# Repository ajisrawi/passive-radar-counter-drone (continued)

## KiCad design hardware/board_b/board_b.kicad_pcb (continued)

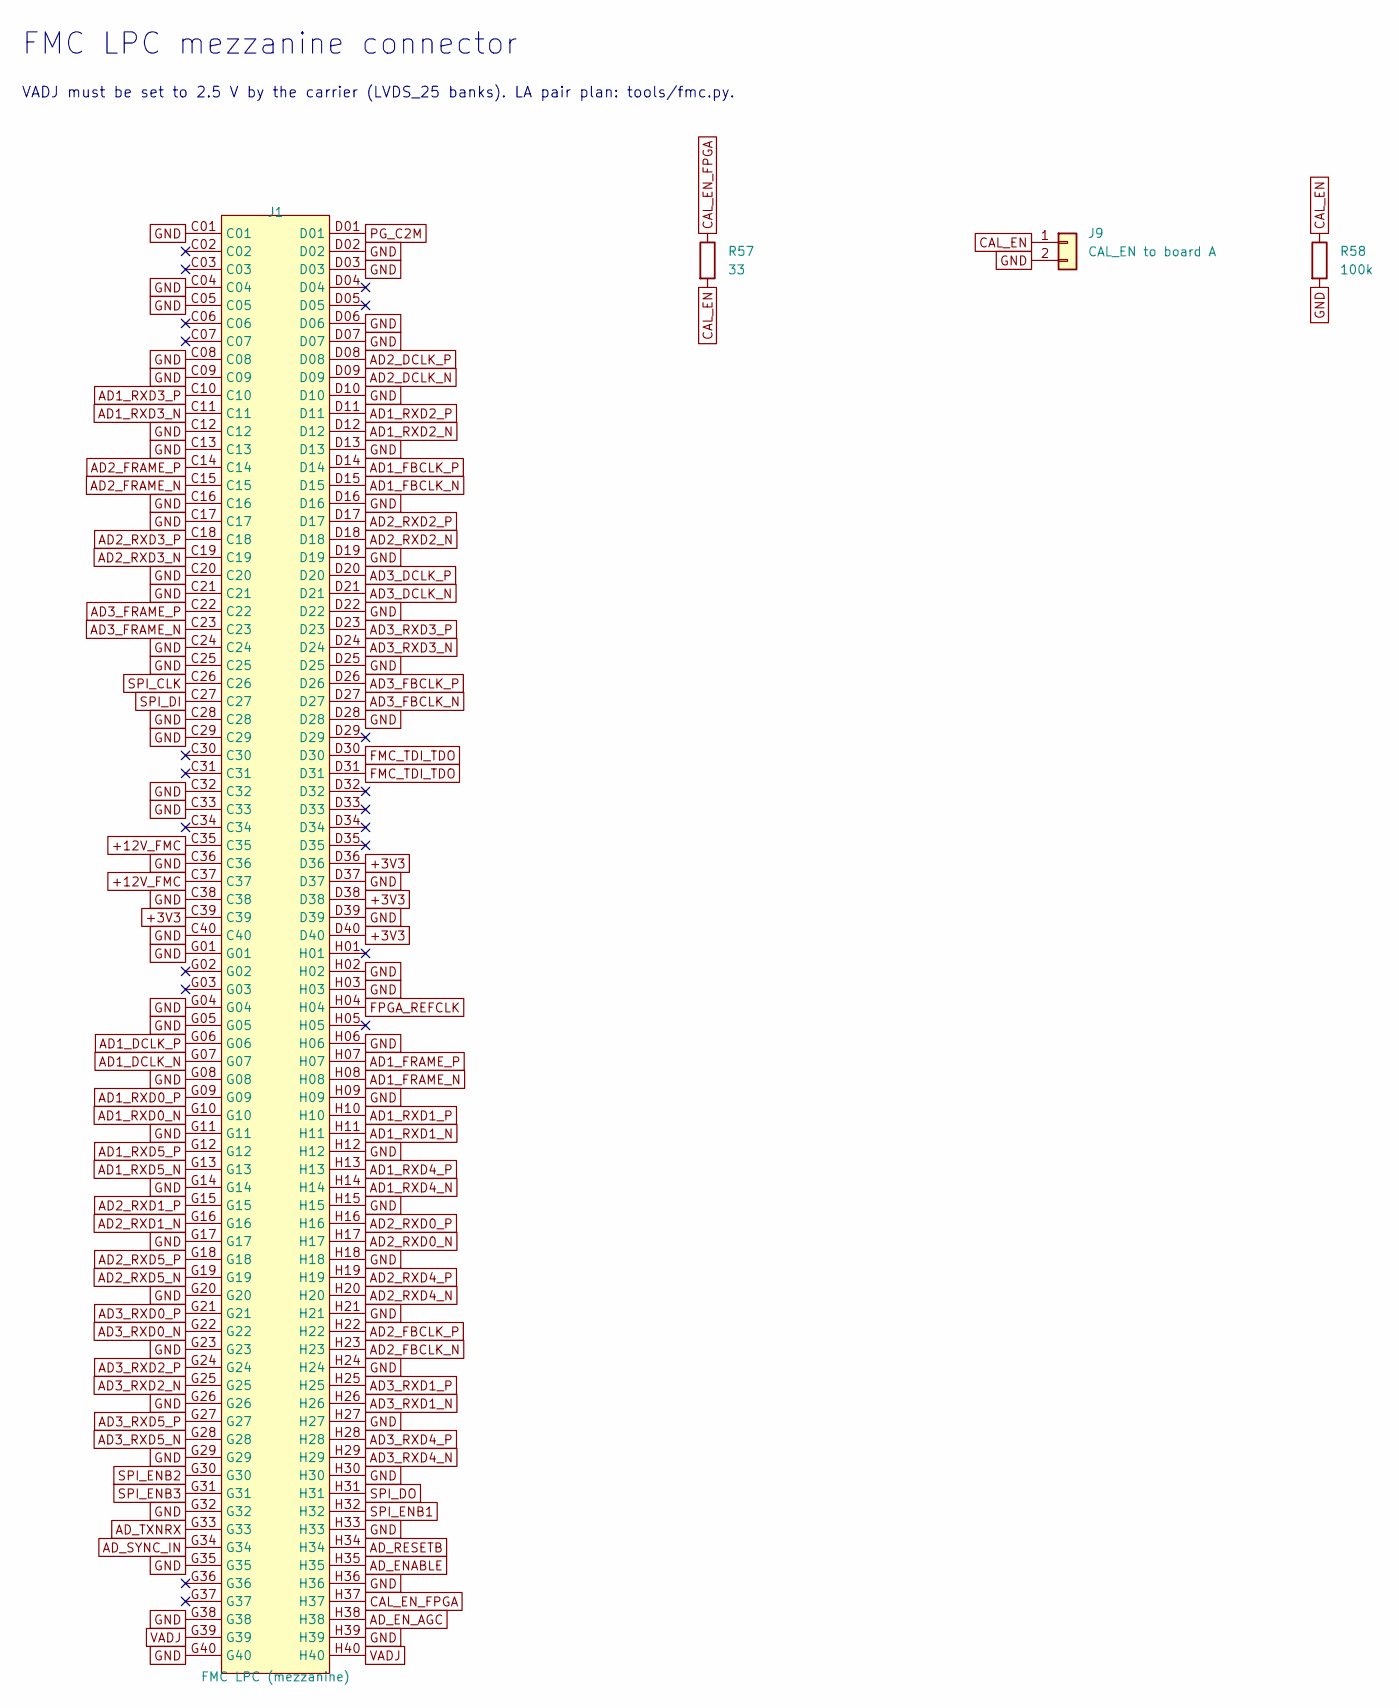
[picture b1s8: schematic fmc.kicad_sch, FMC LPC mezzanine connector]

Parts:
J1: FMC LPC (mezzanine); FPC_SMD_ASP-134604-01; MPN ASP-134604-01; LCSC C2830435
J9: CAL_EN to board A; PinHeader_1x02_P2.54mm_Vertical
R57: 33; R_0402_1005Metric
R58: 100k; R_0402_1005Metric; LCSC C25741

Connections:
+3V3: J1.C39, J1.D36, J1.D38, J1.D40; also elsewhere on the board
+12V_FMC: J1.C35, J1.C37; also elsewhere on the board
AD1_DCLK_N: J1.G07; also elsewhere on the board
AD1_DCLK_P: J1.G06; also elsewhere on the board
AD1_FBCLK_N: J1.D15; also elsewhere on the board
AD1_FBCLK_P: J1.D14; also elsewhere on the board
AD1_FRAME_N: J1.H08; also elsewhere on the board
AD1_FRAME_P: J1.H07; also elsewhere on the board
AD1_RXD0_N: J1.G10; also elsewhere on the board
AD1_RXD0_P: J1.G09; also elsewhere on the board
AD1_RXD1_N: J1.H11; also elsewhere on the board
AD1_RXD1_P: J1.H10; also elsewhere on the board
AD1_RXD2_N: J1.D12; also elsewhere on the board
AD1_RXD2_P: J1.D11; also elsewhere on the board
AD1_RXD3_N: J1.C11; also elsewhere on the board
AD1_RXD3_P: J1.C10; also elsewhere on the board
AD1_RXD4_N: J1.H14; also elsewhere on the board
AD1_RXD4_P: J1.H13; also elsewhere on the board
AD1_RXD5_N: J1.G13; also elsewhere on the board
AD1_RXD5_P: J1.G12; also elsewhere on the board
AD2_DCLK_N: J1.D09; also elsewhere on the board
AD2_DCLK_P: J1.D08; also elsewhere on the board
AD2_FBCLK_N: J1.H23; also elsewhere on the board
AD2_FBCLK_P: J1.H22; also elsewhere on the board
AD2_FRAME_N: J1.C15; also elsewhere on the board
AD2_FRAME_P: J1.C14; also elsewhere on the board
AD2_RXD0_N: J1.H17; also elsewhere on the board
AD2_RXD0_P: J1.H16; also elsewhere on the board
AD2_RXD1_N: J1.G16; also elsewhere on the board
AD2_RXD1_P: J1.G15; also elsewhere on the board
AD2_RXD2_N: J1.D18; also elsewhere on the board
AD2_RXD2_P: J1.D17; also elsewhere on the board
AD2_RXD3_N: J1.C19; also elsewhere on the board
AD2_RXD3_P: J1.C18; also elsewhere on the board
AD2_RXD4_N: J1.H20; also elsewhere on the board
AD2_RXD4_P: J1.H19; also elsewhere on the board
AD2_RXD5_N: J1.G19; also elsewhere on the board
AD2_RXD5_P: J1.G18; also elsewhere on the board
AD3_DCLK_N: J1.D21; also elsewhere on the board
AD3_DCLK_P: J1.D20; also elsewhere on the board
AD3_FBCLK_N: J1.D27; also elsewhere on the board
AD3_FBCLK_P: J1.D26; also elsewhere on the board
AD3_FRAME_N: J1.C23; also elsewhere on the board
AD3_FRAME_P: J1.C22; also elsewhere on the board
AD3_RXD0_N: J1.G22; also elsewhere on the board
AD3_RXD0_P: J1.G21; also elsewhere on the board
AD3_RXD1_N: J1.H26; also elsewhere on the board
AD3_RXD1_P: J1.H25; also elsewhere on the board
AD3_RXD2_N: J1.G25; also elsewhere on the board
AD3_RXD2_P: J1.G24; also elsewhere on the board
AD3_RXD3_N: J1.D24; also elsewhere on the board
AD3_RXD3_P: J1.D23; also elsewhere on the board
AD3_RXD4_N: J1.H29; also elsewhere on the board
AD3_RXD4_P: J1.H28; also elsewhere on the board
AD3_RXD5_N: J1.G28; also elsewhere on the board
AD3_RXD5_P: J1.G27; also elsewhere on the board
AD_ENABLE: J1.H35; also elsewhere on the board
AD_EN_AGC: J1.H38; also elsewhere on the board
AD_RESETB: J1.H34; also elsewhere on the board
AD_SYNC_IN: J1.G34; also elsewhere on the board
AD_TXNRX: J1.G33; also elsewhere on the board
CAL_EN: J9.1, R57.2, R58.1
CAL_EN_FPGA: J1.H37, R57.1
FMC_TDI_TDO: J1.D30, J1.D31
FPGA_REFCLK: J1.H04; also elsewhere on the board
GND: J1.C01, J1.C04, J1.C05, J1.C08, J1.C09, J1.C12, J1.C13, J1.C16, J1.C17, J1.C20, J1.C21, J1.C24, J1.C25, J1.C28, J1.C29, J1.C32, J1.C33, J1.C36, J1.C38, J1.C40, J1.D02, J1.D03, J1.D06, J1.D07, J1.D10, J1.D13, J1.D16, J1.D19, J1.D22, J1.D25, J1.D28, J1.D37, J1.D39, J1.G01, J1.G04, J1.G05, J1.G08, J1.G11, J1.G14, J1.G17, J1.G20, J1.G23, J1.G26, J1.G29, J1.G32, J1.G35, J1.G38, J1.G40, J1.H02, J1.H03, J1.H06, J1.H09, J1.H12, J1.H15, J1.H18, J1.H21, J1.H24, J1.H27, J1.H30, J1.H33, J1.H36, J1.H39, J9.2, R58.2; also elsewhere on the board
PG_C2M: J1.D01; also elsewhere on the board
SPI_CLK: J1.C26; also elsewhere on the board
SPI_DI: J1.C27; also elsewhere on the board
SPI_DO: J1.H31; also elsewhere on the board
SPI_ENB1: J1.H32; also elsewhere on the board
SPI_ENB2: J1.G30; also elsewhere on the board
SPI_ENB3: J1.G31; also elsewhere on the board
VADJ: J1.G39, J1.H40; also elsewhere on the board

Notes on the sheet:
FMC LPC mezzanine connector
VADJ must be set to 2.5 V by the carrier (LVDS_25 banks). LA pair plan: tools/fmc.py.

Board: 8 copper layers, 228 parts (67 on the bottom side), 166 nets, no tracks yet.

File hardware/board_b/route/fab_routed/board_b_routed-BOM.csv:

Comment,Designator,Footprint,JLCPCB Part #
1u,"C1,C7,C12,C14,C17,C19,C23,C29,C34,C36,C39,C41,C45,C51,C56,C58,C61,C63,C106,C112,C118",1,
100n,"C2,C3,C4,C5,C6,C8,C9,C10,C11,C13,C15,C16,C18,C20,C24,C25,C26,C27,C28,C30,C31,C32,C33,C35,C37,C38,C40,C42,C46,C47,C48,C49,C50,C52,C53,C54,C55,C57,C59,C60,C62,C64,C107,C113,C119",1,
100n,"C21,C22,C43,C44,C65,C66,C85,C89,C90,C92,C93,C94,C98,C101,C104,C110,C116",C_0402_1005Metric,
100p,"C67,C68,C70,C71,C73,C74,C76,C77,C79,C80,C82,C83",C_0402_1005Metric,
10u,"C86,C103,C105,C109,C111,C115,C117,C121,C123",C_0603_1608Metric,
1u,"C87,C88,C91,C122,C124",C_0402_1005Metric,
3.3n,C95,C_0402_1005Metric,
10u,"C96,C97,C120",C_0805_2012Metric,
22u,"C99,C100",C_0805_2012Metric,
10n,"C102,C108,C114",C_0402_1005Metric,
600R@100MHz,"FB1,FB2,FB3,FB4,FB5,FB6,FB7,FB8,FB9,FB10,FB11,FB12",L_0603_1608Metric,
FMC LPC (mezzanine),J1,FPC_SMD_ASP-134604-01,
RF_IN0,J2,SMA-TH_BWSMA-KE-Z001,
RF_IN1,J3,SMA-TH_BWSMA-KE-Z001,
RF_IN2,J4,SMA-TH_BWSMA-KE-Z001,
RF_IN3,J5,SMA-TH_BWSMA-KE-Z001,
RF_IN4,J6,SMA-TH_BWSMA-KE-Z001,
RF_IN5,J7,SMA-TH_BWSMA-KE-Z001,
EXT_REF,J8,SMA-TH_BWSMA-KE-Z001,
CAL_EN to board A,J9,PinHeader_1x02_P2.54mm_Vertical,
2.2u,L1,L_Bourns-SRN4018,
14.3k,"R1,R8,R11",R_0402_1005Metric,
22,"R2,R9,R12",R_0402_1005Metric,
10k,"R3,R4,R5,R6,R7,R10,R13,R32,R33,R51,R53,R55",R_0402_1005Metric,
0,"R15,R18,R21,R24,R27,R30",R_0402_1005Metric,
470,R34,R_0402_1005Metric,
1.5k,R36,R_0402_1005Metric,
33,"R37,R40,R43,R46,R57",R_0402_1005Metric,
120,"R38,R41,R44",R_0402_1005Metric,
100,"R39,R42,R45",R_0402_1005Metric,
125k,R47,R_0402_1005Metric,
100k,"R48,R49,R56,R58",R_0402_1005Metric,
16k,"R50,R52,R54",R_0402_1005Metric,
ATB2012-50011,"T1,T2,T3,T4,T5,T6",XFMR-SMD_ATB2012-50011-T000,
AD9361BBCZ,"U1,U2,U3",CSPBGA-144_L10.0-W10.0-R12-C12-P0.80-BL,
TLV75525PDBVR,U4,SOT-23-5,
LMK1C1104PWR,U5,TSSOP-8_L4.4-W3.0-P0.65-LS6.4-TL,
TPS62130RGTR,U6,VQFN-16-1EP_3x3mm_P0.5mm_EP1.68x1.68mm,
ADP1755ACPZ-R7,"U7,U8,U9",LFCSP-16_L4.0-W4.0-P0.65-BL-EP2.2,
40MHz TCXO 0.5ppm,Y1,OSC-SMD_10P-L7.0-W5.0-BL,

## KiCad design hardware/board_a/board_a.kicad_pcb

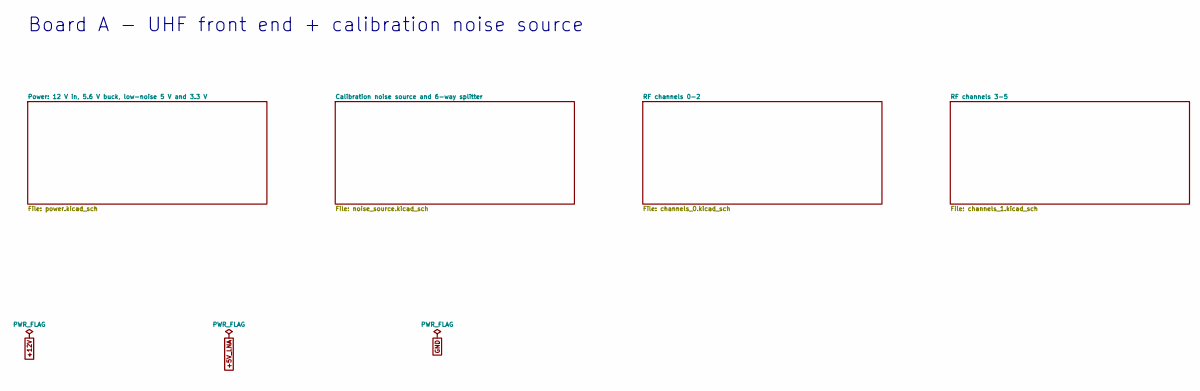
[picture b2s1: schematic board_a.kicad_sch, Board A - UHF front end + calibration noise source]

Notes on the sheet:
Board A - UHF front end + calibration noise source

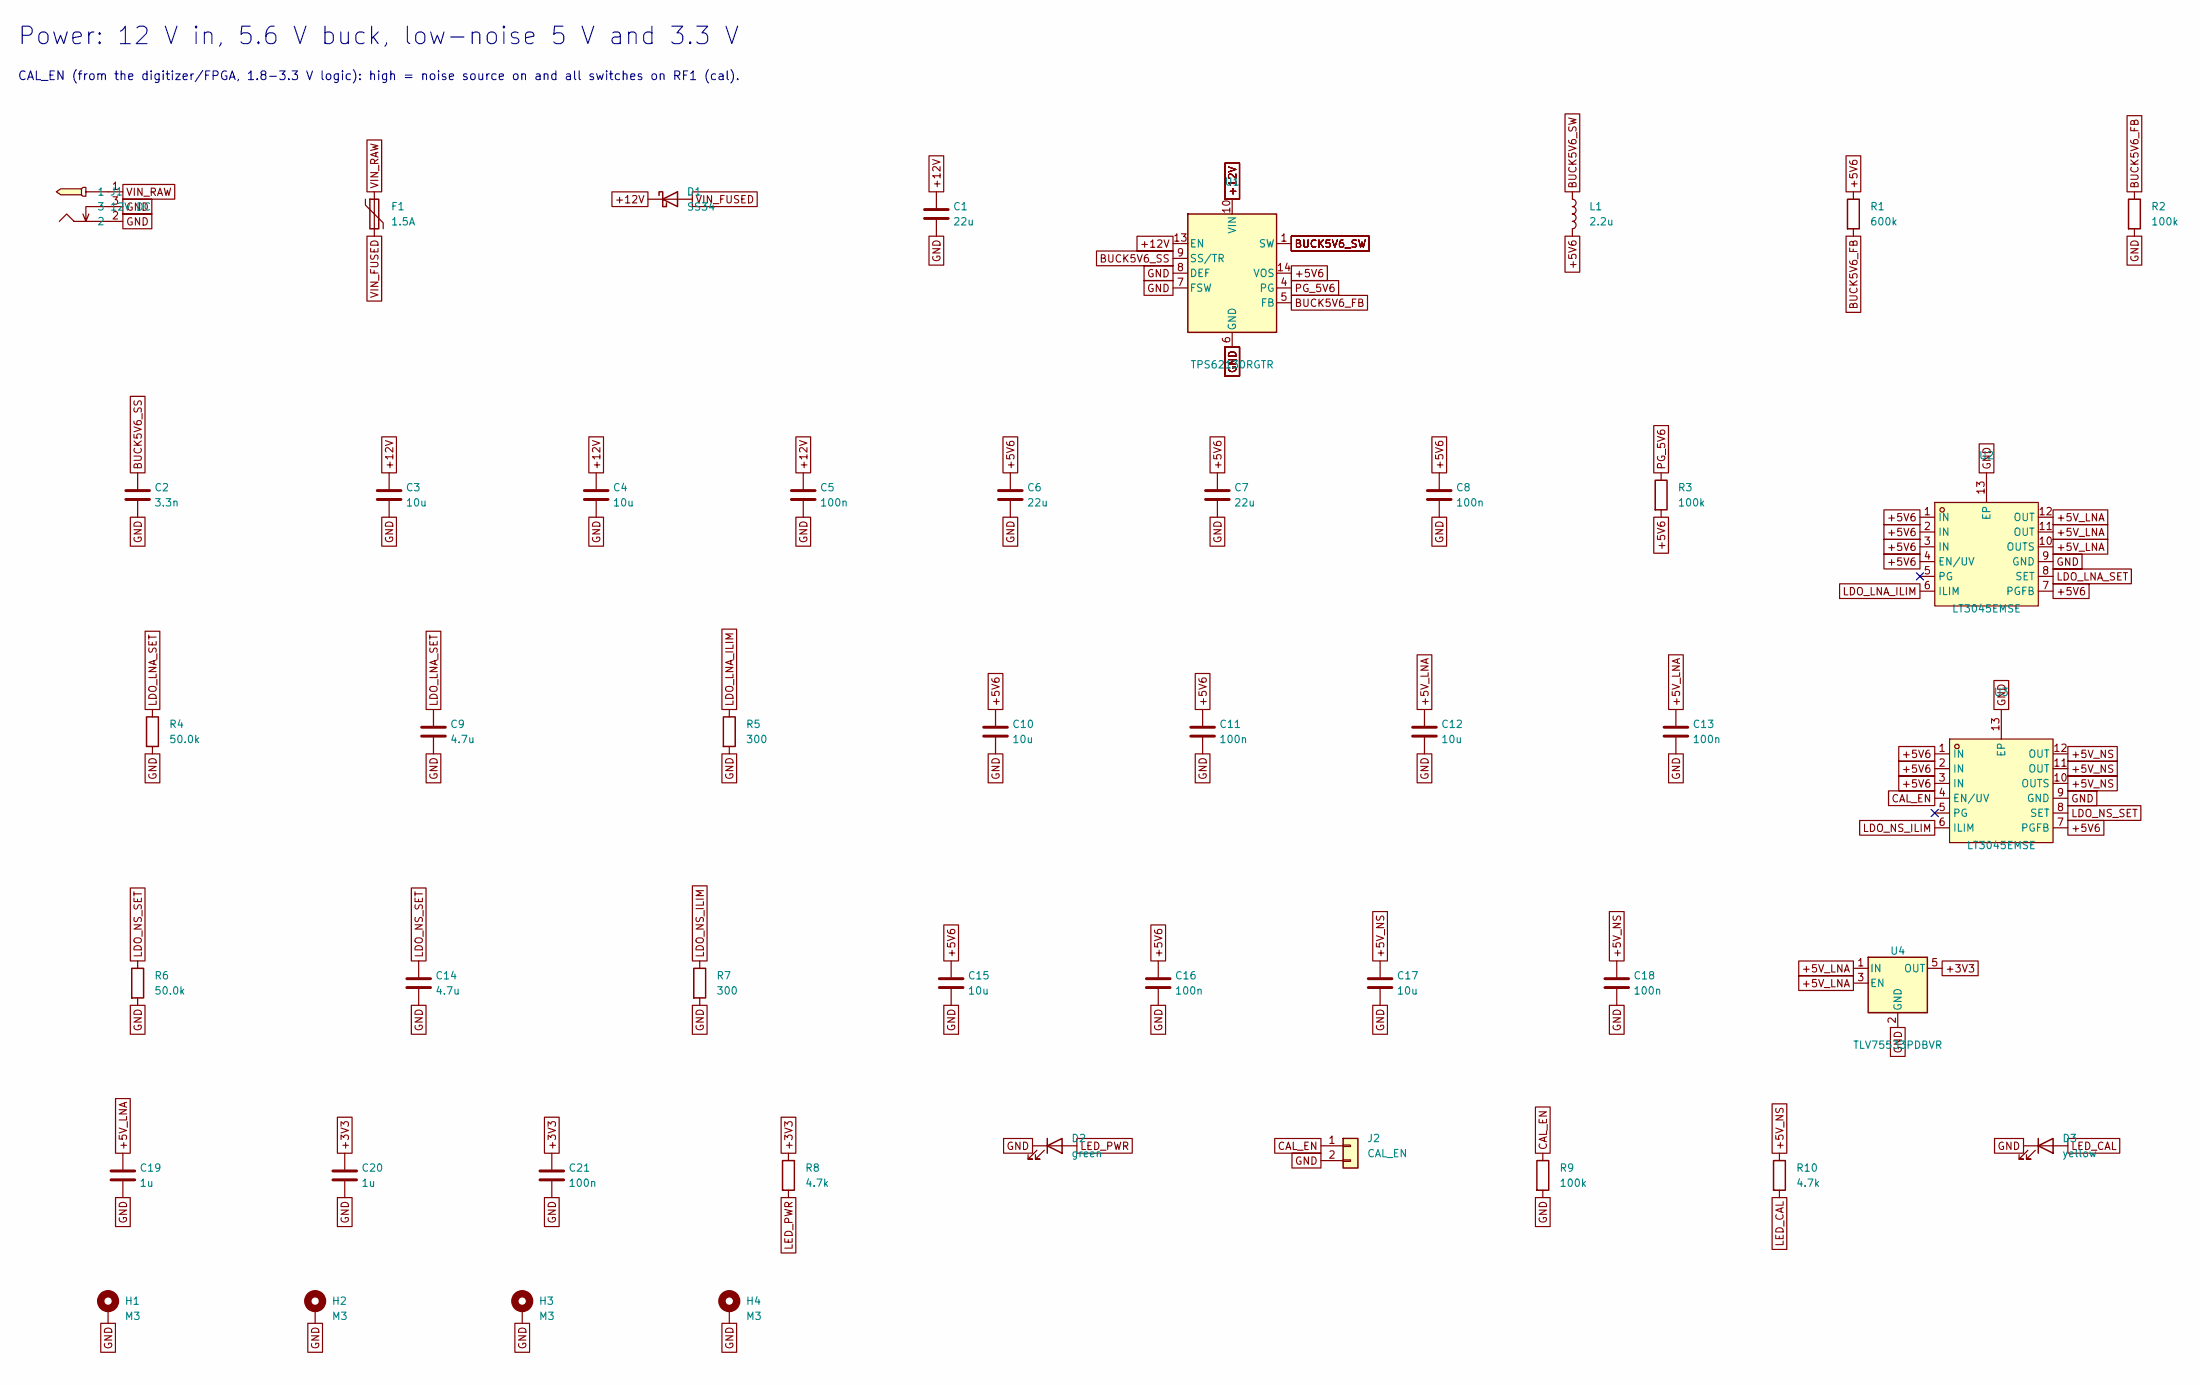
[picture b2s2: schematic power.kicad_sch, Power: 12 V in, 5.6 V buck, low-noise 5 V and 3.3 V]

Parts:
C1: 22u; C_1206_3216Metric
C2: 3.3n; C_0402_1005Metric
C3, C4: 10u; C_0805_2012Metric
C5, C8, C11, C13, C16, C18, C21: 100n; C_0402_1005Metric; LCSC C1525
C6, C7: 22u; C_0805_2012Metric; LCSC C45783
C9, C14: 4.7u; C_0603_1608Metric
C10, C12, C15, C17: 10u; C_0603_1608Metric; LCSC C19702
C19, C20: 1u; C_0402_1005Metric; LCSC C52923
D1: SS34; D_SMA; MPN SS34; LCSC C8678
D2: green; LED_0603_1608Metric
D3: yellow; LED_0603_1608Metric
F1: 1.5A; Fuse_1206_3216Metric
H1, H2, H3, H4: M3; MountingHole_3.2mm_M3_Pad_Via
J1: 12V DC; DC-IN-TH_DC-005C-20A; MPN DC-005C-20A; LCSC C84007
J2: CAL_EN; PinHeader_1x02_P2.54mm_Vertical
L1: 2.2u; L_Bourns-SRN4018; MPN SRN4018-2R2M
R1: 600k; R_0402_1005Metric
R2, R3, R9: 100k; R_0402_1005Metric; LCSC C25741
R4, R6: 50.0k; R_0402_1005Metric; Tolerance 0.1%
R5, R7: 300; R_0402_1005Metric
R8, R10: 4.7k; R_0402_1005Metric; LCSC C25900
U1: TPS62130RGTR; VQFN-16-1EP_3x3mm_P0.5mm_EP1.68x1.68mm; MPN TPS62130RGTR; LCSC C43590
U2, U3: LT3045EMSE; MSOP-12_L4.0-W3.0-P0.65-LS4.9-BL-EP; MPN LT3045EMSE#PBF; LCSC C580012
U4: TLV75533PDBVR; SOT-23-5; LCSC C404027

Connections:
+3V3: C20.1, C21.1, R8.1, U4.5 (OUT); also elsewhere on the board
+5V6: C6.1, C7.1, C8.1, C10.1, C11.1, C15.1, C16.1, L1.2, R1.1, R3.2, U1.14 (VOS), U2.1 (IN), U2.2 (IN), U2.3 (IN), U2.4 (EN/UV), U2.7 (PGFB), U3.1 (IN), U3.2 (IN), U3.3 (IN), U3.7 (PGFB)
+5V_LNA: C12.1, C13.1, C19.1, U2.10 (OUTS), U2.11 (OUT), U2.12 (OUT), U4.1 (IN), U4.3 (EN); also elsewhere on the board
+5V_NS: C17.1, C18.1, R10.1, U3.10 (OUTS), U3.11 (OUT), U3.12 (OUT); also elsewhere on the board
+12V: C1.1, C3.1, C4.1, C5.1, D1.1 (K), U1.10 (VIN), U1.11 (VIN), U1.12 (VIN), U1.13 (EN)
BUCK5V6_FB: R1.2, R2.1, U1.5 (FB)
BUCK5V6_SS: C2.1, U1.9 (SS/TR)
BUCK5V6_SW: L1.1, U1.1 (SW), U1.2 (SW), U1.3 (SW)
CAL_EN: J2.1, R9.1, U3.4 (EN/UV); also elsewhere on the board
GND: C1.2, C2.2, C3.2, C4.2, C5.2, C6.2, C7.2, C8.2, C9.2, C10.2, C11.2, C12.2, C13.2, C14.2, C15.2, C16.2, C17.2, C18.2, C19.2, C20.2, C21.2, D2.1 (K), D3.1 (K), H1.1, H2.1, H3.1, H4.1, J1.2, J1.3, J2.2, R2.2, R4.2, R5.2, R6.2, R7.2, R9.2, U1.6 (GND), U1.7 (FSW), U1.8 (DEF), U1.15 (GND), U1.16 (GND), U1.17 (GND), U2.9 (GND), U2.13 (EP), U3.9 (GND), U3.13 (EP), U4.2 (GND); also elsewhere on the board
LDO_LNA_ILIM: R5.1, U2.6 (ILIM)
LDO_LNA_SET: C9.1, R4.1, U2.8 (SET)
LDO_NS_ILIM: R7.1, U3.6 (ILIM)
LDO_NS_SET: C14.1, R6.1, U3.8 (SET)
LED_CAL: D3.2 (A), R10.2
LED_PWR: D2.2 (A), R8.2
PG_5V6: R3.1, U1.4 (PG)
VIN_FUSED: D1.2 (A), F1.2
VIN_RAW: F1.1, J1.1

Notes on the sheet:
Power: 12 V in, 5.6 V buck, low-noise 5 V and 3.3 V
CAL_EN (from the digitizer/FPGA, 1.8-3.3 V logic): high = noise source on and all switches on RF1 (cal).

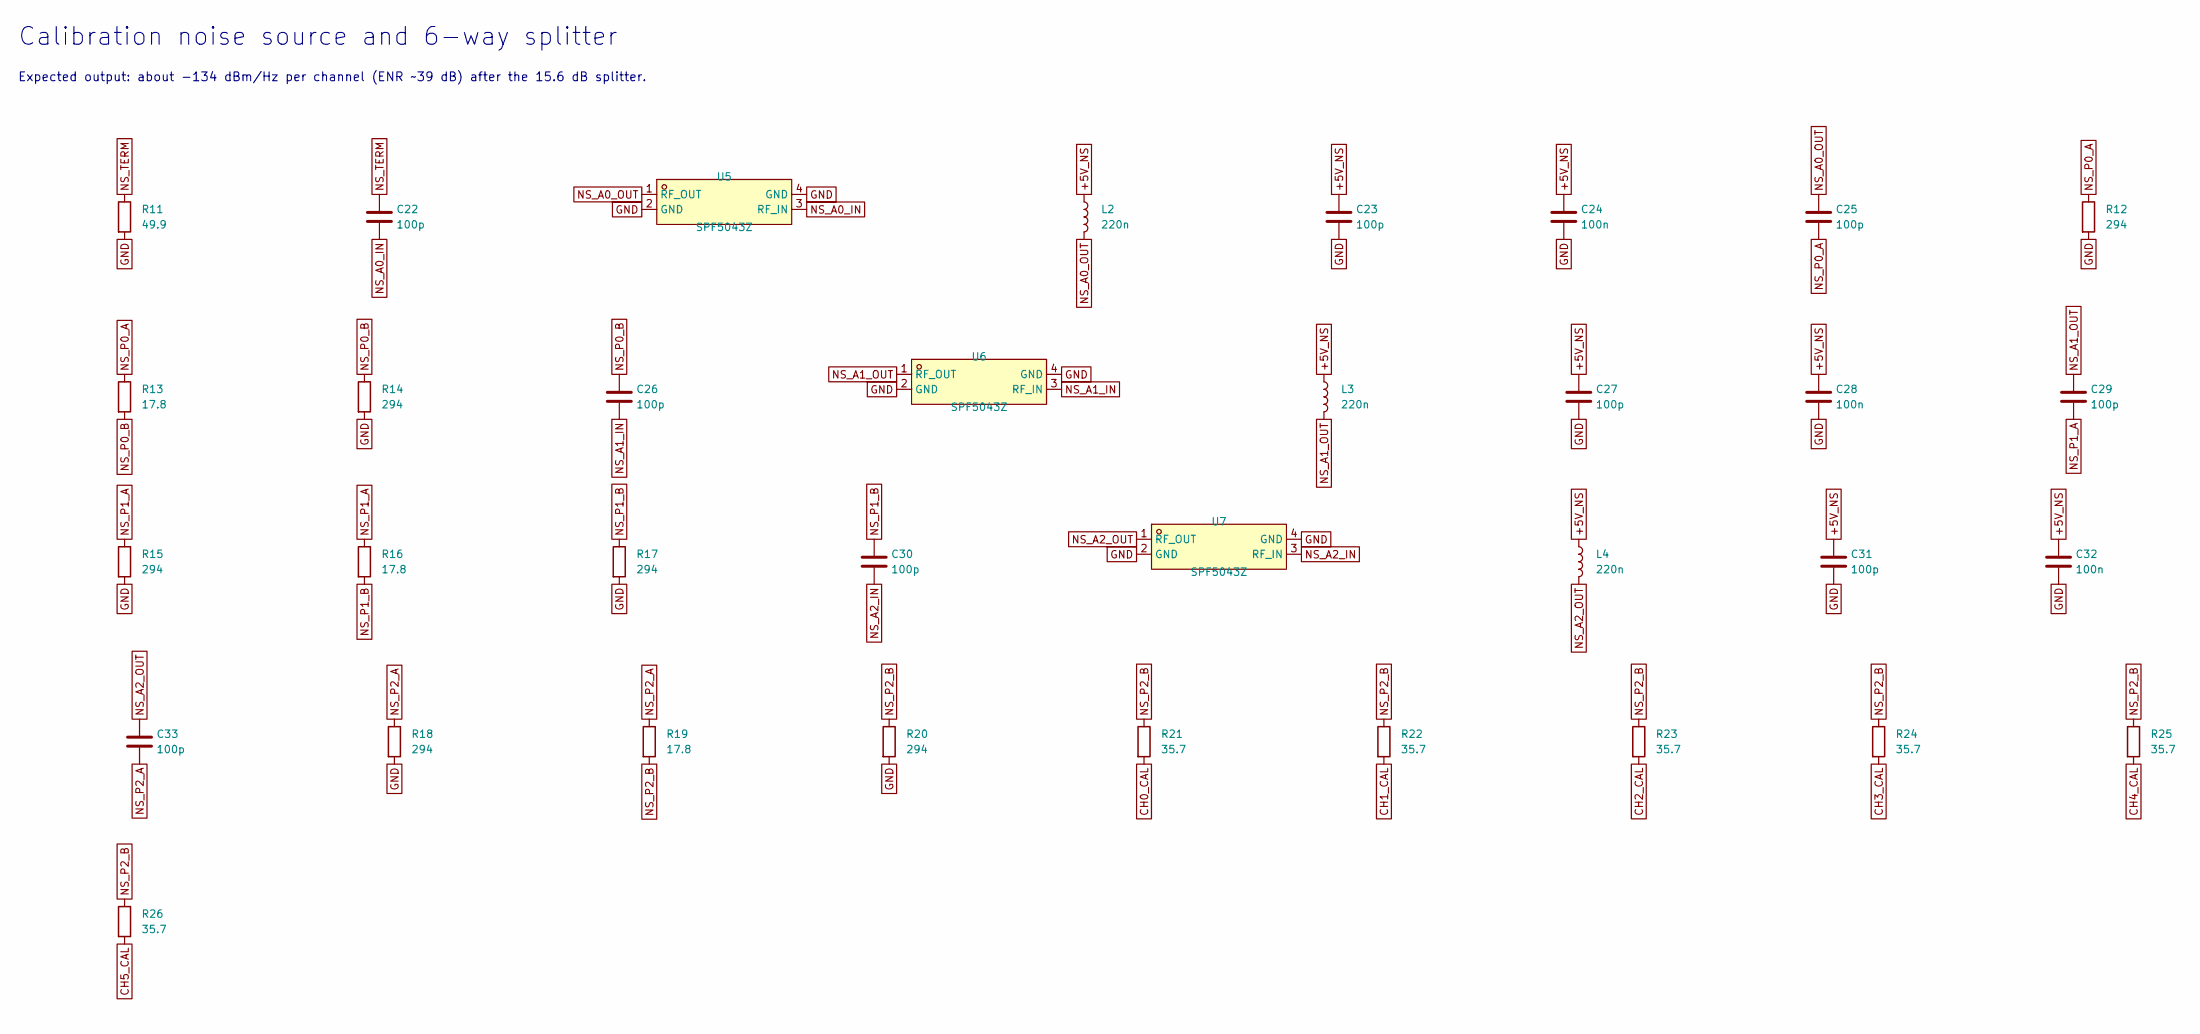
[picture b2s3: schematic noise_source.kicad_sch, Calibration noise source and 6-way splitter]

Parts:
C22, C23, C25, C26, C27, C29, C30, C31, C33: 100p; C_0402_1005Metric
C24, C28, C32: 100n; C_0402_1005Metric; LCSC C1525
L2, L3, L4: 220n; L_0603_1608Metric
R11: 49.9; R_0402_1005Metric
R12, R14, R15, R17, R18, R20: 294; R_0402_1005Metric
R13, R16, R19: 17.8; R_0402_1005Metric
R21, R22, R23, R24, R25, R26: 35.7; R_0402_1005Metric
U5, U6, U7: SPF5043Z; SOT343_L2.0-W1.3-P1.30-LS2.1-BL; MPN SPF5043Z; LCSC C470902

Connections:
+5V_NS: C23.1, C24.1, C27.1, C28.1, C31.1, C32.1, L2.1, L3.1, L4.1; also elsewhere on the board
CH0_CAL: R21.2; also elsewhere on the board
CH1_CAL: R22.2; also elsewhere on the board
CH2_CAL: R23.2; also elsewhere on the board
CH3_CAL: R24.2; also elsewhere on the board
CH4_CAL: R25.2; also elsewhere on the board
CH5_CAL: R26.2; also elsewhere on the board
GND: C23.2, C24.2, C27.2, C28.2, C31.2, C32.2, R11.2, R12.2, R14.2, R15.2, R17.2, R18.2, R20.2, U5.2 (GND), U5.4 (GND), U6.2 (GND), U6.4 (GND), U7.2 (GND), U7.4 (GND); also elsewhere on the board
NS_A0_IN: C22.2, U5.3 (RF_IN)
NS_A0_OUT: C25.1, L2.2, U5.1 (RF_OUT)
NS_A1_IN: C26.2, U6.3 (RF_IN)
NS_A1_OUT: C29.1, L3.2, U6.1 (RF_OUT)
NS_A2_IN: C30.2, U7.3 (RF_IN)
NS_A2_OUT: C33.1, L4.2, U7.1 (RF_OUT)
NS_P0_A: C25.2, R12.1, R13.1
NS_P0_B: C26.1, R13.2, R14.1
NS_P1_A: C29.2, R15.1, R16.1
NS_P1_B: C30.1, R16.2, R17.1
NS_P2_A: C33.2, R18.1, R19.1
NS_P2_B: R19.2, R20.1, R21.1, R22.1, R23.1, R24.1, R25.1, R26.1
NS_TERM: C22.1, R11.1

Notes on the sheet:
Calibration noise source and 6-way splitter
Expected output: about -134 dBm/Hz per channel (ENR ~39 dB) after the 15.6 dB splitter.

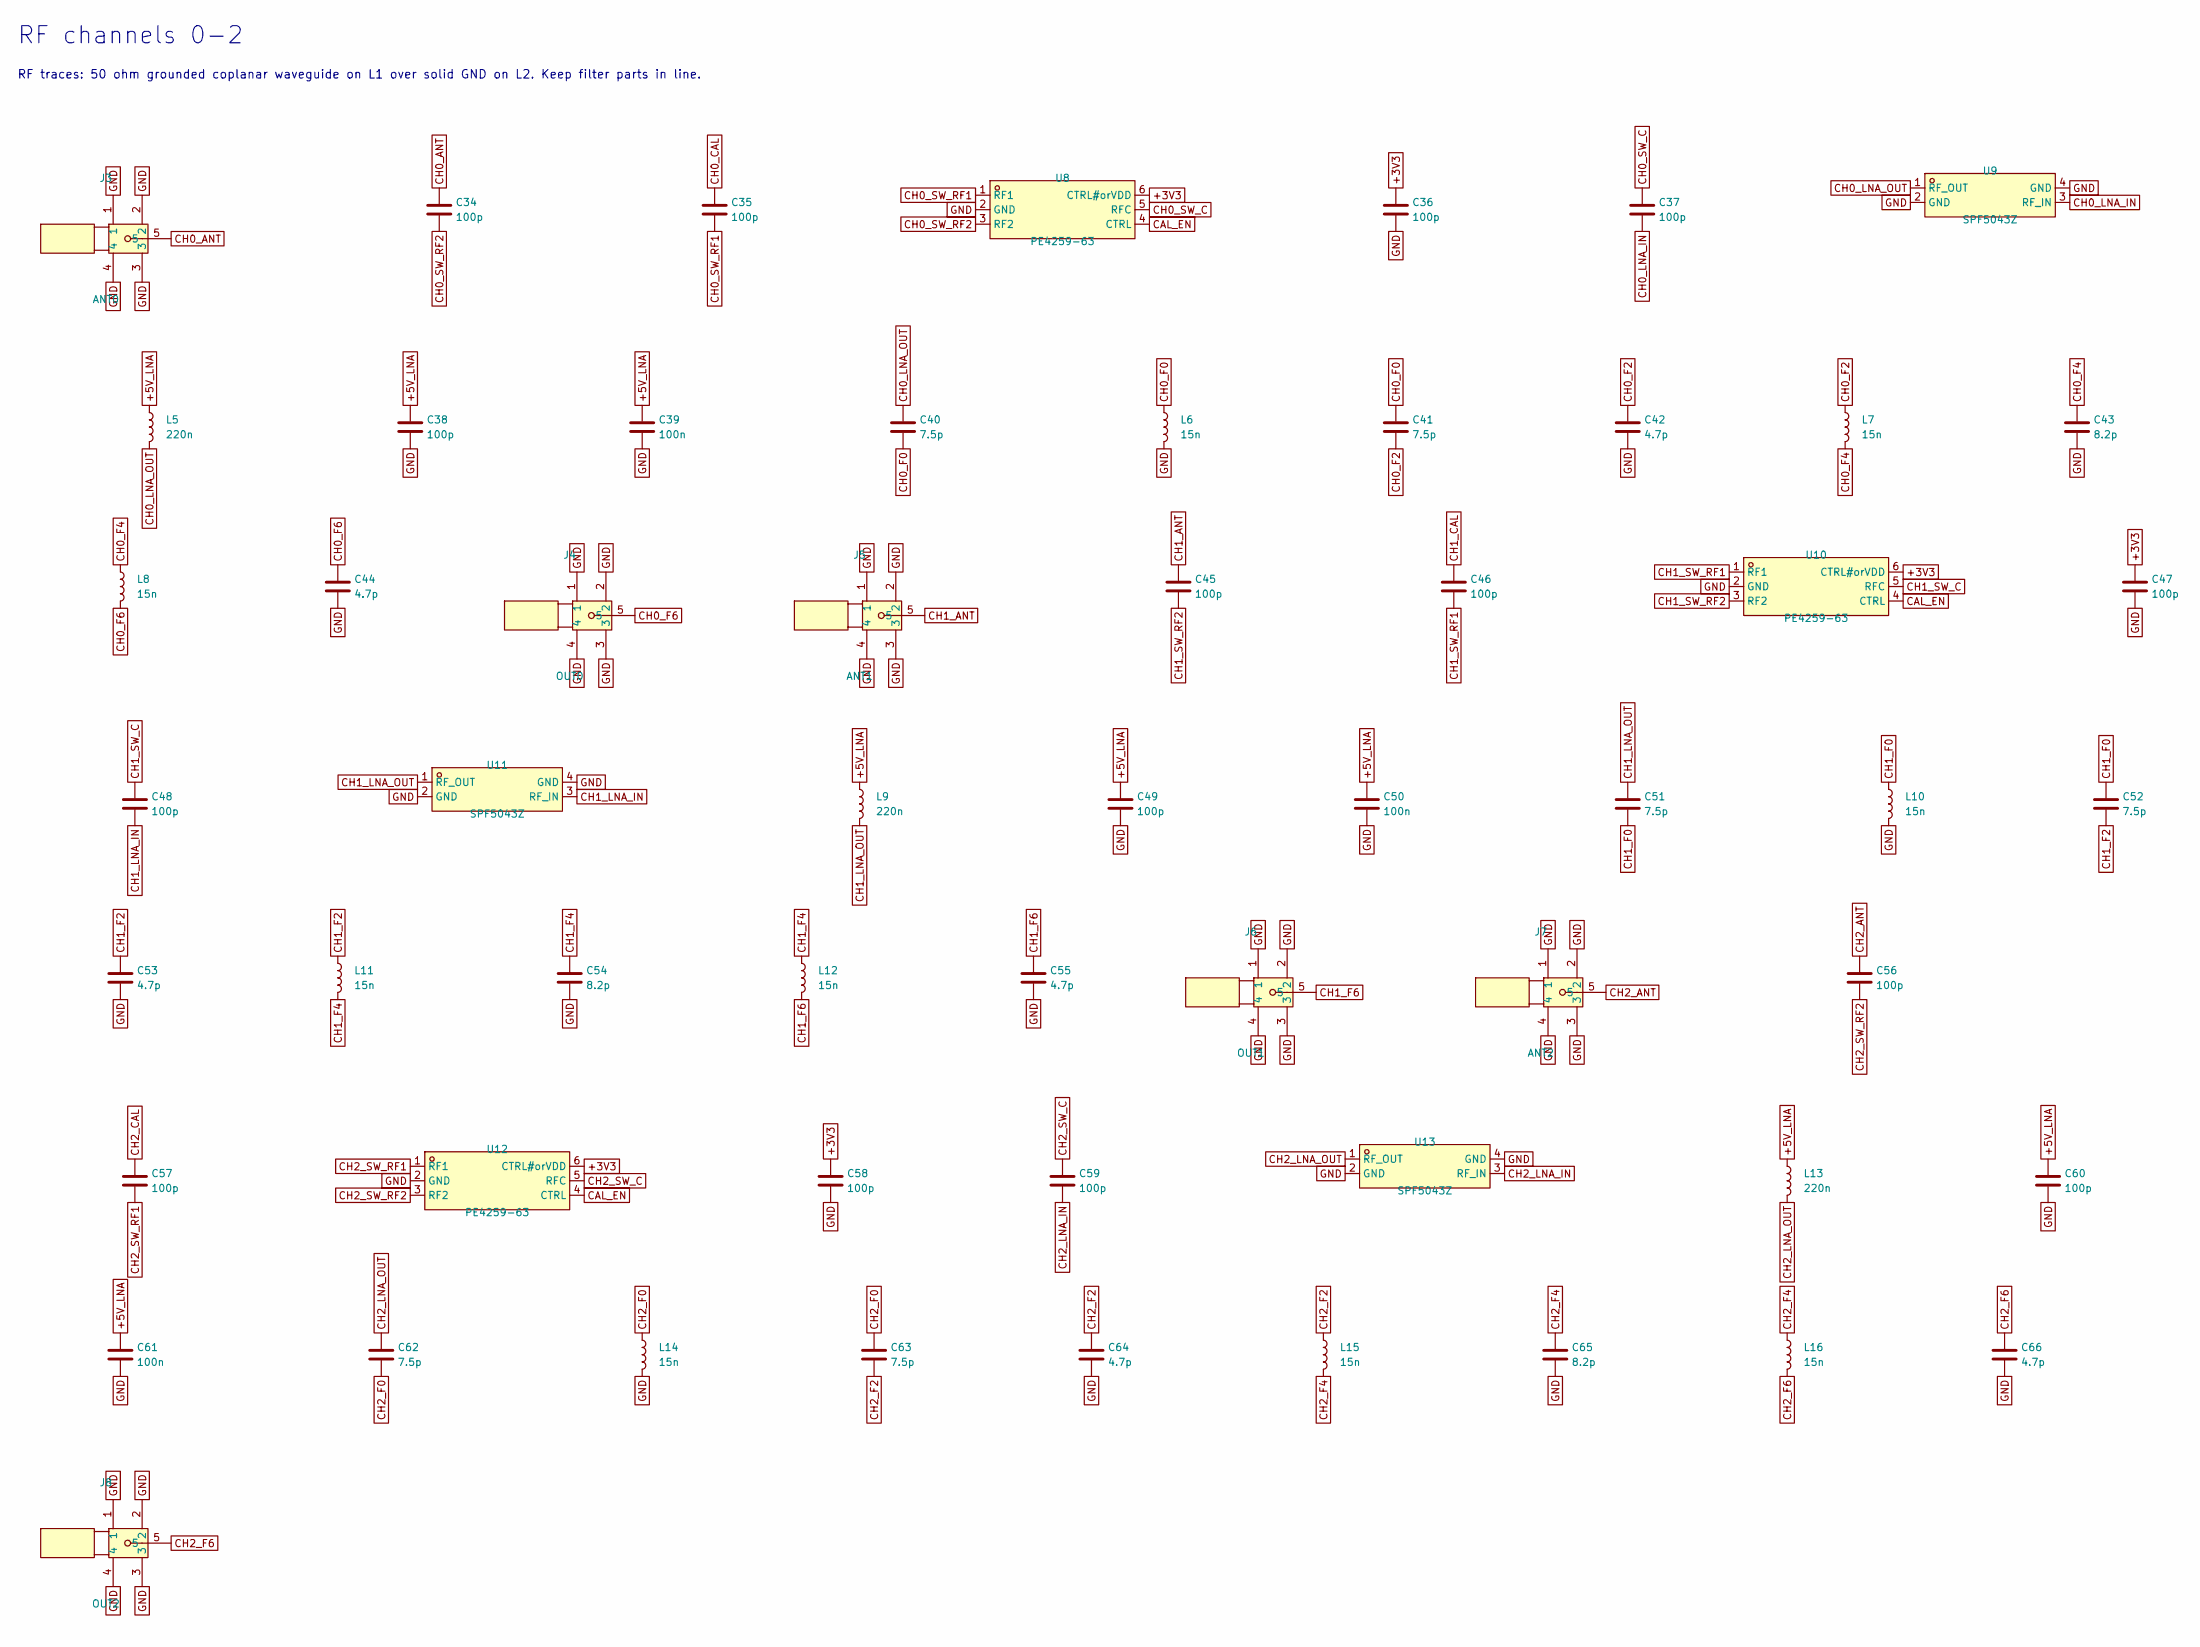
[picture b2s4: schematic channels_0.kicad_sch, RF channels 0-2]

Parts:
C34, C35, C36, C37, C38, C45, C46, C47, C48, C49, C56, C57, C58, C59, C60: 100p; C_0402_1005Metric
C39, C50, C61: 100n; C_0402_1005Metric; LCSC C1525
C40, C41, C51, C52, C62, C63: 7.5p; C_0402_1005Metric
C42, C44, C53, C55, C64, C66: 4.7p; C_0402_1005Metric
C43, C54, C65: 8.2p; C_0402_1005Metric
J3: ANT0; SMA-TH_BWSMA-KE-Z001; MPN BWSMA-KE-Z001; LCSC C496549
J4: OUT0; SMA-TH_BWSMA-KE-Z001; MPN BWSMA-KE-Z001; LCSC C496549
J5: ANT1; SMA-TH_BWSMA-KE-Z001; MPN BWSMA-KE-Z001; LCSC C496549
J6: OUT1; SMA-TH_BWSMA-KE-Z001; MPN BWSMA-KE-Z001; LCSC C496549
J7: ANT2; SMA-TH_BWSMA-KE-Z001; MPN BWSMA-KE-Z001; LCSC C496549
J8: OUT2; SMA-TH_BWSMA-KE-Z001; MPN BWSMA-KE-Z001; LCSC C496549
L5, L9, L13: 220n; L_0603_1608Metric
L6, L7, L8, L10, L11, L12, L14, L15, L16: 15n; L_0402_1005Metric
U8, U10, U12: PE4259-63; SC-70-6_L2.2-W1.3-P0.65-LS2.1-BL; MPN PE4259-63; LCSC C470892
U9, U11, U13: SPF5043Z; SOT343_L2.0-W1.3-P1.30-LS2.1-BL; MPN SPF5043Z; LCSC C470902

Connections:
+3V3: C36.1, C47.1, C58.1, U8.6 (CTRL#orVDD), U10.6 (CTRL#orVDD), U12.6 (CTRL#orVDD); also elsewhere on the board
+5V_LNA: C38.1, C39.1, C49.1, C50.1, C60.1, C61.1, L5.1, L9.1, L13.1; also elsewhere on the board
CAL_EN: U8.4 (CTRL), U10.4 (CTRL), U12.4 (CTRL); also elsewhere on the board
CH0_ANT: C34.1, J3.5
CH0_CAL: C35.1; also elsewhere on the board
CH0_F0: C40.2, C41.1, L6.1
CH0_F2: C41.2, C42.1, L7.1
CH0_F4: C43.1, L7.2, L8.1
CH0_F6: C44.1, J4.5, L8.2
CH0_LNA_IN: C37.2, U9.3 (RF_IN)
CH0_LNA_OUT: C40.1, L5.2, U9.1 (RF_OUT)
CH0_SW_C: C37.1, U8.5 (RFC)
CH0_SW_RF1: C35.2, U8.1 (RF1)
CH0_SW_RF2: C34.2, U8.3 (RF2)
CH1_ANT: C45.1, J5.5
CH1_CAL: C46.1; also elsewhere on the board
CH1_F0: C51.2, C52.1, L10.1
CH1_F2: C52.2, C53.1, L11.1
CH1_F4: C54.1, L11.2, L12.1
CH1_F6: C55.1, J6.5, L12.2
CH1_LNA_IN: C48.2, U11.3 (RF_IN)
CH1_LNA_OUT: C51.1, L9.2, U11.1 (RF_OUT)
CH1_SW_C: C48.1, U10.5 (RFC)
CH1_SW_RF1: C46.2, U10.1 (RF1)
CH1_SW_RF2: C45.2, U10.3 (RF2)
CH2_ANT: C56.1, J7.5
CH2_CAL: C57.1; also elsewhere on the board
CH2_F0: C62.2, C63.1, L14.1
CH2_F2: C63.2, C64.1, L15.1
CH2_F4: C65.1, L15.2, L16.1
CH2_F6: C66.1, J8.5, L16.2
CH2_LNA_IN: C59.2, U13.3 (RF_IN)
CH2_LNA_OUT: C62.1, L13.2, U13.1 (RF_OUT)
CH2_SW_C: C59.1, U12.5 (RFC)
CH2_SW_RF1: C57.2, U12.1 (RF1)
CH2_SW_RF2: C56.2, U12.3 (RF2)
GND: C36.2, C38.2, C39.2, C42.2, C43.2, C44.2, C47.2, C49.2, C50.2, C53.2, C54.2, C55.2, C58.2, C60.2, C61.2, C64.2, C65.2, C66.2, J3.1, J3.2, J3.3, J3.4, J4.1, J4.2, J4.3, J4.4, J5.1, J5.2, J5.3, J5.4, J6.1, J6.2, J6.3, J6.4, J7.1, J7.2, J7.3, J7.4, J8.1, J8.2, J8.3, J8.4, L6.2, L10.2, L14.2, U8.2 (GND), U9.2 (GND), U9.4 (GND), U10.2 (GND), U11.2 (GND), U11.4 (GND), U12.2 (GND), U13.2 (GND), U13.4 (GND); also elsewhere on the board

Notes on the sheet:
RF channels 0-2
RF traces: 50 ohm grounded coplanar waveguide on L1 over solid GND on L2. Keep filter parts in line.
